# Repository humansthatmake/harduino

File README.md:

<h3><strong>THE HARDUINO</strong></h3>

<p style="text-align: left;">
    Harduino is an Arduino Compatible Input/Output Board that uses the same microcontroller as most <a href="https://www.arduino.cc/">Arduino boards</a>, the <a href="http://www.atmel.com/images/Atmel-8271-8-bit-AVR-Microcontroller-ATmega48A-48PA-88A-88PA-168A-168PA-328-328P_datasheet_Complete.pdf">ATmega328P</a>.
</p>

<p>
    To get started please refer to the following page:
    <a href="http://humansthatmake.com/harduino">humansthatmake.com/harduino</a>
</p>

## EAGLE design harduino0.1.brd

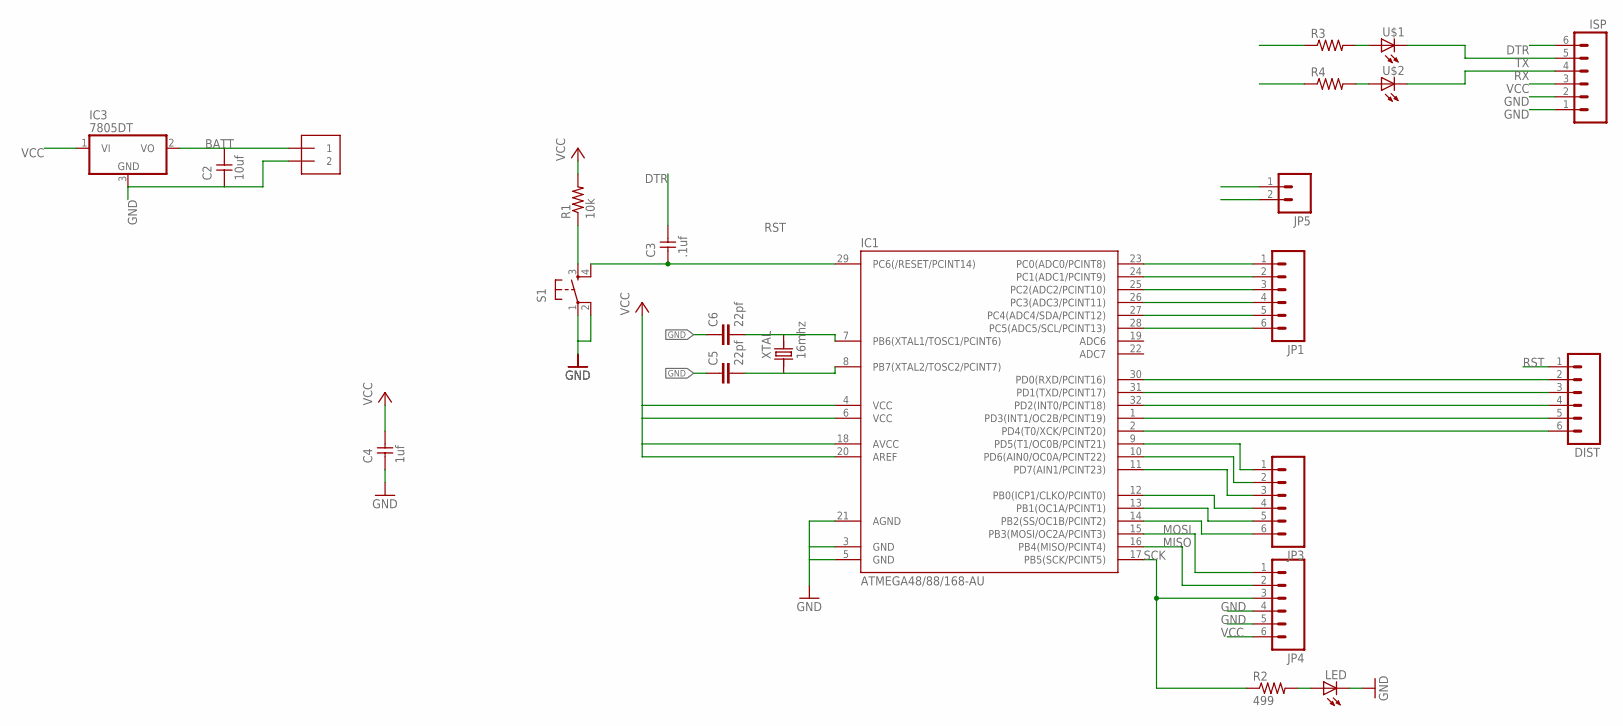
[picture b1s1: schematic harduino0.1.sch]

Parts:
C2: 10uf; 1206
C3: .1uf; 1206
C4: 1uf; 1206
C5, C6: 22pf; 1206
DIST: M06LONGPADS; 1X06_LONGPADS
IC1: ATMEGA48/88/168-AU; TQFP32-08
IC3: 7805DT; TO252
ISP: M06SMD; 1X06-SMD
J1: 1X2-3.5MM; 3.5MMTERM
JP1, JP3, JP4: M06LONGPADS; 1X06_LONGPADS
JP5: M02; 1X02_LONGPADS
LED: LED1206; 1206
R1: 10k; 1206
R2: 499; 1206
R3, R4: RESISTOR1206; 1206
S1: 6MM_SWITCH6MM_SWITCH; 6MM_SWITCH
U$1, U$2: LED1206; 1206
XTAL: 16mhz; CS10

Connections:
BATT: C2.2, IC3.2 (VO), J1.1
DTR: C3.2, ISP.6
GND: C2.1, C4.1, C5.1, C6.1, IC1.3 (GND), IC1.5 (GND), IC1.21 (AGND), IC3.3 (GND), ISP.1, ISP.2, J1.2, JP4.4, JP4.5, JP5.1, LED.2 (C), S1.1, S1.2 (P1)
MISO: IC1.16 (PB4(MISO/PCINT4)), JP4.2
MOSI: IC1.15 (PB3(MOSI/OC2A/PCINT3)), JP4.1
unnamed: C6.2, IC1.7 (PB6(XTAL1/TOSC1/PCINT6)), XTAL.P$2 (2)
unnamed: C5.2, IC1.8 (PB7(XTAL2/TOSC2/PCINT7)), XTAL.P$1 (1)
unnamed: IC1.23 (PC0(ADC0/PCINT8)), JP1.1
unnamed: IC1.24 (PC1(ADC1/PCINT9)), JP1.2
unnamed: IC1.25 (PC2(ADC2/PCINT10)), JP1.3
unnamed: IC1.26 (PC3(ADC3/PCINT11)), JP1.4
unnamed: IC1.27 (PC4(ADC4/SDA/PCINT12)), JP1.5
unnamed: IC1.28 (PC5(ADC5/SCL/PCINT13)), JP1.6
unnamed: DIST.4, IC1.32 (PD2(INT0/PCINT18))
unnamed: DIST.5, IC1.1 (PD3(INT1/OC2B/PCINT19))
unnamed: DIST.6, IC1.2 (PD4(T0/XCK/PCINT20))
unnamed: IC1.9 (PD5(T1/OC0B/PCINT21)), JP3.1
unnamed: IC1.10 (PD6(AIN0/OC0A/PCINT22)), JP3.2
unnamed: IC1.11 (PD7(AIN1/PCINT23)), JP3.3
unnamed: IC1.12 (PB0(ICP1/CLKO/PCINT0)), JP3.4
unnamed: IC1.13 (PB1(OC1A/PCINT1)), JP3.5
unnamed: IC1.14 (PB2(SS/OC1B/PCINT2)), JP3.6
unnamed: DIST.2, IC1.30 (PD0(RXD/PCINT16)), R4.1
unnamed: R4.2, U$2.1 (A)
unnamed: R1.1, S1.3 (S)
unnamed: R3.2, U$1.1 (A)
unnamed: LED.1 (A), R2.2
unnamed: DIST.3, IC1.31 (PD1(TXD/PCINT17)), R3.1
RST: C3.1, DIST.1, IC1.29 (PC6(/RESET/PCINT14)), S1.4 (S1)
RX: ISP.4, U$2.2 (C)
SCK: IC1.17 (PB5(SCK/PCINT5)), JP4.3, R2.1
TX: ISP.5, U$1.2 (C)
VCC: C4.2, IC1.4 (VCC), IC1.6 (VCC), IC1.18 (AVCC), IC1.20 (AREF), IC3.1 (VI), ISP.3, JP4.6, JP5.2, R1.2

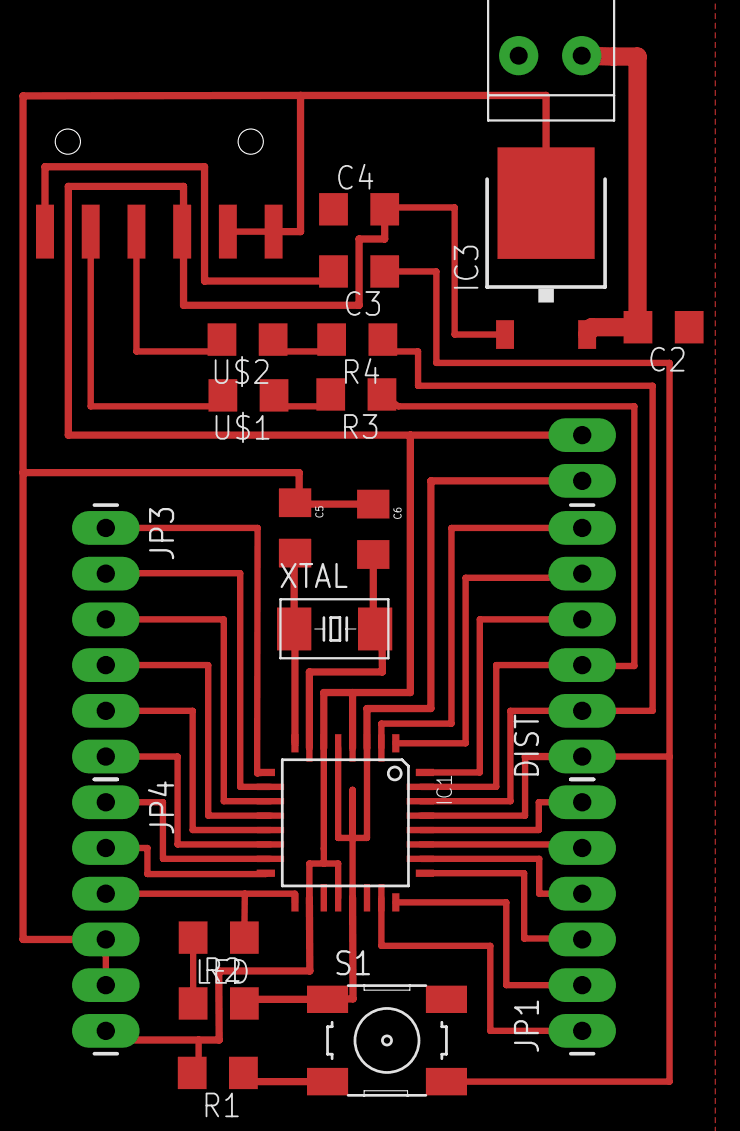
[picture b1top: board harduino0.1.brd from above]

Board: 2 copper layers, 23 parts (0 on the bottom side), 33 nets.

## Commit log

2016-07-01 harduino
    update 0.2
2016-07-05 vreg bug fix
    vreg was inverted
2016-07-05 removing autosaves

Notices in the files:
parts and their libraries:
01_SparkFun: Licensing: CC v3.0 Share-Alike You are welcome to use this library for commercial purposes.
